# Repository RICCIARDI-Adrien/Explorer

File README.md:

# Explorer

A small wheeled robot based on a PIC18F26K22 microcontroller and a single ultrasonic distance sensor.  
The goal was to develop and test two basic artificial intelligence algorithms, both relying only on the ultrasonic sensor :
- The robot moves at will in a room and must avoid obstacles. It must never remain stuck.
- The robot is idle, waiting for a moving object to come close to it. Then, it must follow the moving object, staying at a safe distance. If the moving object comes too close from the robot, the robot must escape.

## Hardware

## Build tools
The schematics and PCB were drawn using Cadsoft Eagle 6.6.0.  
The microcontroller firmware is built with SourceBoost 7.30.  
The Command Line Interface program can be built under Linux using gcc or under Windows with Cygwin or MinGW.

## Photo gallery

### Chassis construction

Start with two 200x90x2mm galvanized steel plates :

One plate will be the chassis bottom. Make holes for servomotor support flat angle brackets and screw them :

Here is the other side :

Now screw the free wheel :

Add the screws that will hold the chassis upper plate :

### Motors assembly

Here are the servomotors :

Screw them into supports :

### Voltage regulator assembly

Screw voltage regulator to chassis bottom plate. This allows to use the whole chassis as heat sink.

### Chassis upper part

Drill holes for LED, switch and serial communication connector, then screw them. Also add the nuts and bolts that will hold the battery pack.

Solder battery pack coupler to a little piece of PCB (don't forget to isolate terminals). This way, when coupler wires will break (it just a matter of time before it happens), it is easy to repair without having to disassemble the chassis.

Solder LED, switch and connector wires :

### Electronic board

Board is made of test PCB soldered by hand.

Here is the board screwed to the chassis bottom :

### Fully assembled robot

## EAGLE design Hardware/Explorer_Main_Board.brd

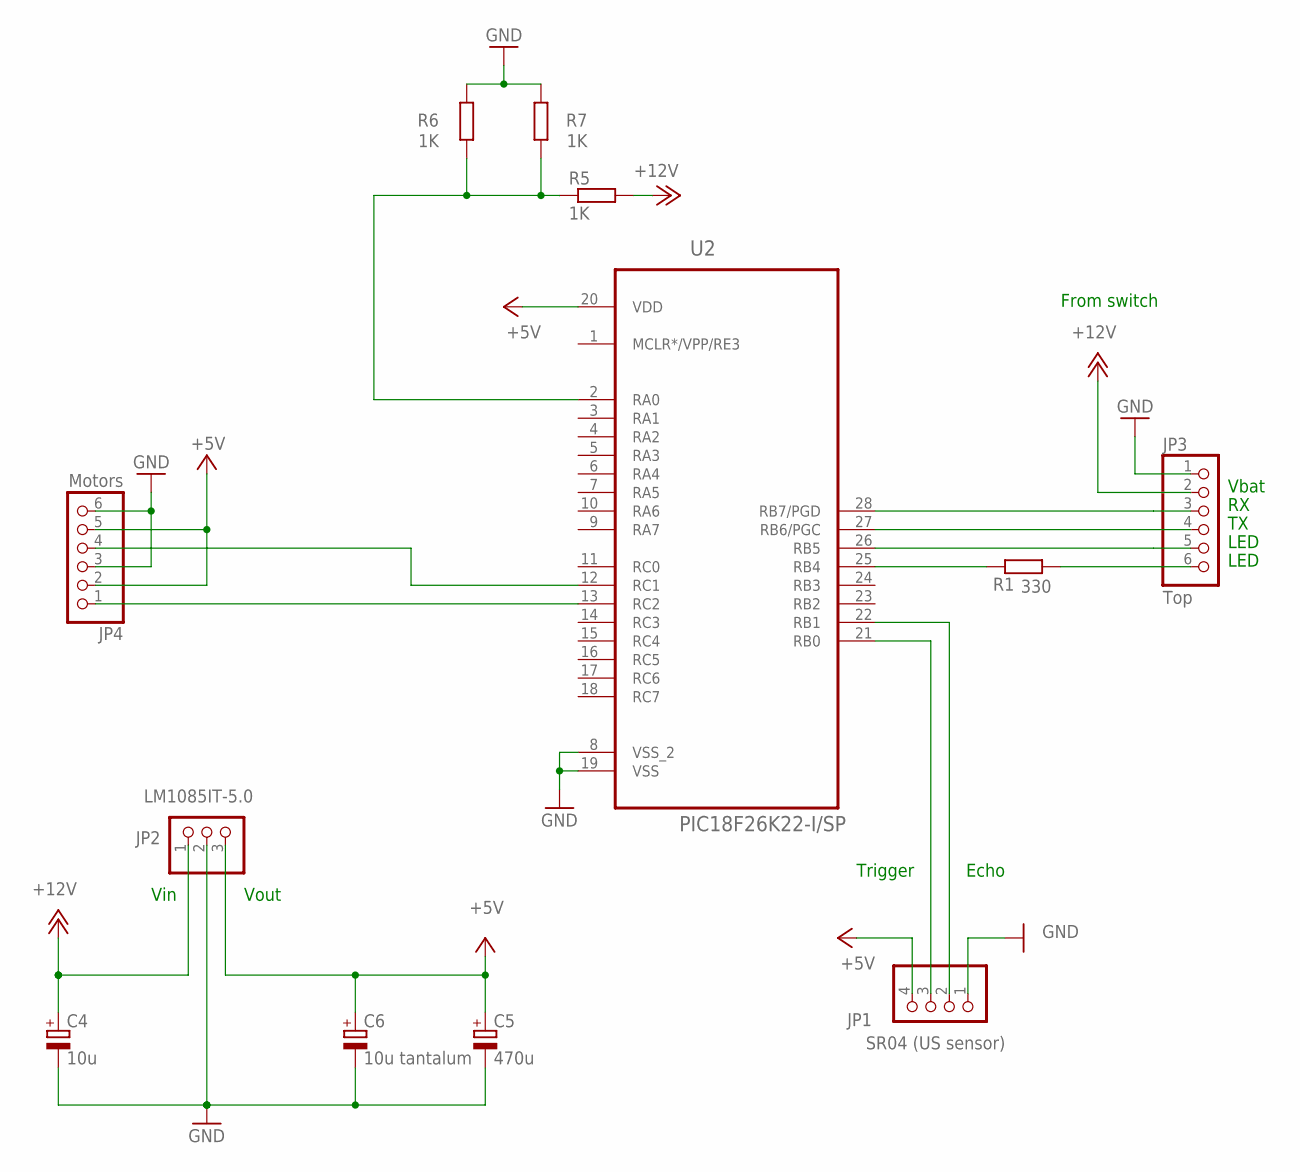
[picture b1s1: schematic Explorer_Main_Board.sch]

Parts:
C4: 10u; E2,5-6E
C5: 470u; E5-8,5
C6: 10u tantalum; E2,5-6E
JP1: SR04 (US sensor); 1X04
JP2: LM1085IT-5.0; 1X03
JP3: Top; 1X06
JP4: Motors; 1X06
R1: 330; 0207/12
R5, R6, R7: 1K; 0207/12
U2: PIC18F26K22-I/SP; DIP254P762X508-28P

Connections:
+5V: C5.+, C6.+, JP1.4, JP2.3, JP4.2, JP4.5, U2.20 (VDD)
+12V: C4.+, JP2.1, JP3.2, R5.2
GND: C4.-, C5.-, C6.-, JP1.1, JP2.2, JP3.1, JP4.3, JP4.6, R6.2, R7.2, U2.8 (VSS_2), U2.19 (VSS)
unnamed: JP3.6, R1.1
unnamed: R1.2, U2.25 (RB4)
unnamed: JP1.2, U2.22 (RB1)
unnamed: JP1.3, U2.21 (RB0)
unnamed: R5.1, R6.1, R7.1, U2.2 (RA0)
unnamed: JP3.3, U2.28 (RB7/PGD)
unnamed: JP3.4, U2.27 (RB6/PGC)
unnamed: JP4.4, U2.12 (RC1)
unnamed: JP4.1, U2.13 (RC2)
unnamed: JP3.5, U2.26 (RB5)

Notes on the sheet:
Vbat
From switch
LED
Vin
Vout
Echo
Trigger

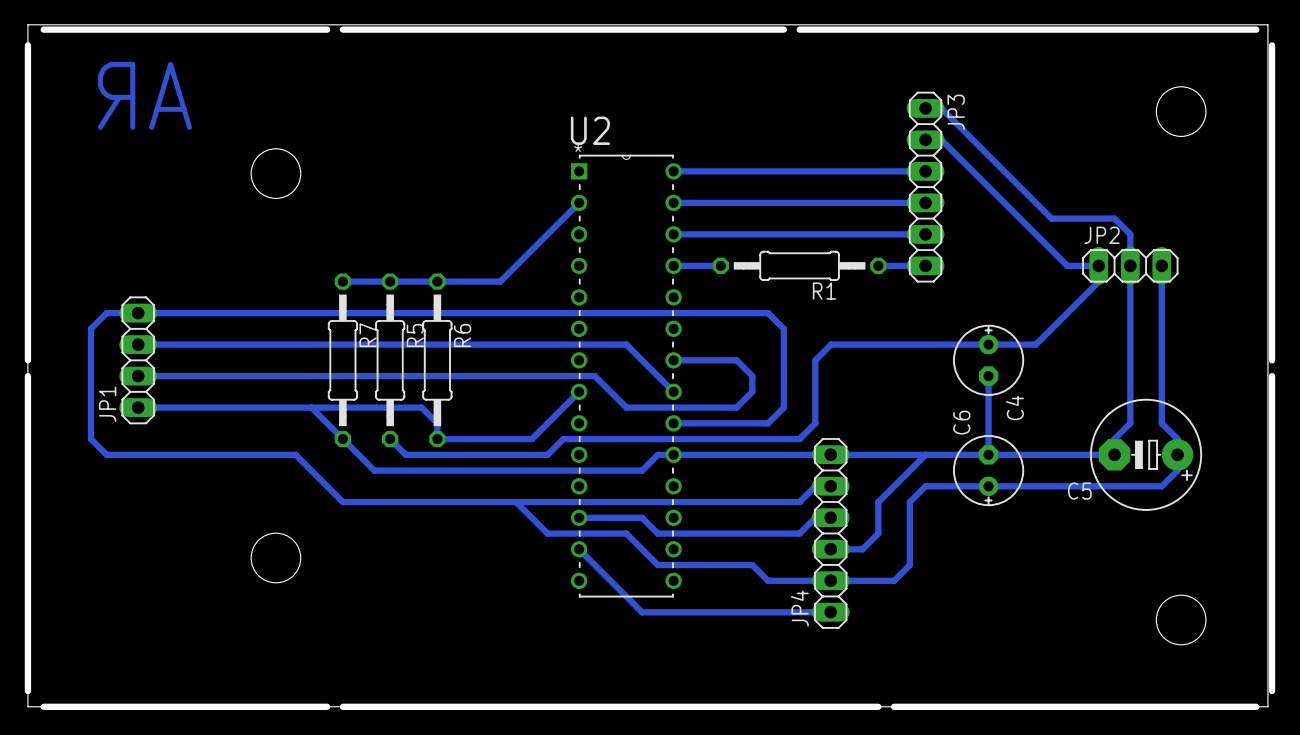
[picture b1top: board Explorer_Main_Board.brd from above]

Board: 2 copper layers, 100.3 x 54.7 mm, 12 parts (0 on the bottom side), 13 nets.

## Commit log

2015-07-19 Added schematics and PCB.
2015-09-28 Added the bootloader and the firmware source directories. The firmware interrupt-driven UART is working.
2015-09-29 Added the battery voltage sampling code.
2015-10-07 The bootloader and the firmware update tool are working.
2015-10-07 Improved the update tool to a command line interface handling all the robot features.
2015-10-10 Added a detection of the currently running program (bootloader or firmware) to make the upgrading command fully automatic.
2015-10-10 Added the bootloader support to the firmware.
2015-10-11 Motors are working.
2015-10-11 Distance sensor is working.
2015-10-18 Made a simpler bootloader that do not rely on the firmware code to work.
2015-10-30 Fixed a bug in the command line interface that omitted the last instructions when flashing a firmware.
2015-10-30 Made a cleaner cast of a bootloader variable.
2015-10-30 Improved the UART code and adapted it to the new bootloader.
2015-10-30 Reorganized some motors initialization intructions into a more coherent order.
2015-10-30 Force the shared timer to immediately trigger an interrupt in order to fastly sample a distance value.
2015-10-30 Removed the clock initialization in the firmware as it is already initialized by the bootloader.
2015-10-30 Added a timer to handle the distance sensor trigger pin.
2015-10-30 Added the 'avoid obstacles' IA behaviour.
2015-10-30 Added a weak battery protection code.
2015-10-31 Improved the 'avoid obstacles' IA. The robot turns faster and is now able to go backward if the detected obstacles are too close.
2015-11-03 Improved the distance sensor sampling time.
2015-11-07 Added a new IA that avoids objects by turning randomly to left or right and a pseudo-random number generator.
2015-11-14 Improved the 'avoid objects by randomly turning' AI.
2015-12-29 Added several software timers instead of only a single one.
2015-12-29 Added a delayed mechanism to the AI that avoids the objects by randomly turning which makes the robot come nearer to the obstacles while it is not scared by the obstacle proximity.
2015-12-30 The robot can now choose between 4 angles when turning to avoid an obstacle.
2016-11-26 Replaced the Command Line Interface tool internal UART library by a git sub-module of the Serial Port library to keep it up to date.
2016-11-26 Updated README with web site URL and build tools information.
2016-11-26 Updated Eagle project to Eagle 7.5.0 and improved schematics names displaying.
2016-11-26 Displayed the schematics on the README.
2016-11-27 Moved AI algorithms in separate files.
2017-01-21 Made the 'avoid objects' AI behavior change direction if the robot is going straight since several seconds.
2017-05-08 Automated distance measuring to avoid hanging artificial intelligence algorithm loops with unpredictable delays.
2017-05-08 Started 'follow object' artificial intelligence algorithm implementation.
2017-05-08 Improved 'follow object' behaviour by learning in which direction the object moved last time.
2017-05-08 Removed unused header inclusion.
2017-05-08 Added 'escaping' capability when an object comes too close during the 'follow object' behaviour.
2020-09-05 Added robot goal description and presentation picture to README.md.
2020-09-05 Added chassis construction pictures and brief instructions to README.md.
2020-09-05 Moved schematic picture to resources directory.
2020-09-05 Added motors assembly and voltage regulator assembly pictures and instructions to README.md.
2020-09-05 Added chassis upper part assembly pictures and instructions to README.md.
2020-09-05 Added electronic board pictures to README.md.
2020-09-05 Added fully assembled robot pictures to README.md.
2020-09-05 Removed firmware .hex file from repository.
